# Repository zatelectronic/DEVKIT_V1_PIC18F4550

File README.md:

<div align="center">

# DEVKIT V1 PIC18F4550

**Kit de desenvolvimento profissional para o microcontrolador PIC18F4550 com USB nativo, programação via conector ICSP compatível com programador externo, reguladores 5V e 3,3V, oscilador SMD, botões RESET e BOOT, 2 LEDs de status e exposição completa de todos os ports GPIO**

</div>

---

## 📋 Índice

- [DEVKIT V1 PIC18F4550](#devkit-v1-pic18f4550)
  - [📋 Índice](#-índice)
  - [Visão Geral](#visão-geral)
  - [Renders 3D](#renders-3d)
  - [Arquitetura do Projeto](#arquitetura-do-projeto)
  - [Funcionalidades](#funcionalidades)
  - [Especificações Técnicas](#especificações-técnicas)
  - [Arquitetura de Alimentação](#arquitetura-de-alimentação)
  - [Interface USB Nativa](#interface-usb-nativa)
  - [Conector ICSP — Programação](#conector-icsp--programação)
    - [J5 — ICSP Principal (6 pinos angulado)](#j5--icsp-principal-6-pinos-angulado)
    - [J6 — Conector Auxiliar (3 pinos)](#j6--conector-auxiliar-3-pinos)
  - [Mapa Completo de Conectores e GPIO](#mapa-completo-de-conectores-e-gpio)
    - [J1 — Alimentação Externa (2 pinos)](#j1--alimentação-externa-2-pinos)
    - [J2 — Port RA (5 pinos)](#j2--port-ra-5-pinos)
    - [J3 — Port RC Superior (3 pinos)](#j3--port-rc-superior-3-pinos)
    - [J4 — Port RC Inferior (6 pinos)](#j4--port-rc-inferior-6-pinos)
    - [J7 — Port RE (4 pinos)](#j7--port-re-4-pinos)
    - [J8 — Port RB (4 pinos)](#j8--port-rb-4-pinos)
    - [J9 — Port RD (8 pinos)](#j9--port-rd-8-pinos)
    - [J10 — Alimentações (3 pinos)](#j10--alimentações-3-pinos)
  - [Lista de Materiais](#lista-de-materiais)
    - [Microcontrolador](#microcontrolador)
    - [USB Type-C e Alimentação](#usb-type-c-e-alimentação)
    - [Programador ICSP](#programador-icsp)
    - [Conectores GPIO](#conectores-gpio)
  - [Estrutura do Repositório](#estrutura-do-repositório)
  - [Como Usar](#como-usar)
    - [1. Gravando firmware via ICSP](#1-gravando-firmware-via-icsp)
    - [2. Alimentação](#2-alimentação)
    - [3. Modo Bootloader USB (BOOT)](#3-modo-bootloader-usb-boot)
    - [Exemplo de código — MPLAB XC8](#exemplo-de-código--mplab-xc8)
    - [Ferramentas recomendadas](#ferramentas-recomendadas)
  - [Sobre](#sobre)

---

## Visão Geral

**DEVKIT V1 PIC18F4550** é um kit de desenvolvimento completo para o microcontrolador **PIC18F4550-IPT** (TQFP-44 SMD), projetado pela **ZAT ELECTRONIC** utilizando **KiCad 10** com esquemático hierárquico dividido em quatro sub-folhas: **Microcontrolador**, **USB Type-C**, **Programador ICSP** e **Conexões GPIO**.

O PIC18F4550 é um microcontrolador de 8 bits da família PIC18 com **USB 2.0 Full Speed nativo** (RC4/D− e RC5/D+), memória Flash de 32KB, SRAM de 2KB e EEPROM de 256 bytes. O DEVKIT expõe todos os ports GPIO (RA, RB, RC, RD, RE) em conectores fêmea de 2,54mm, inclui reguladores de tensão **5V** e **3,3V** on-board, oscilador a cristal SMD de **8MHz**, botões **RESET** e **BOOT** tácteis SMD, **2 LEDs SMD** de status e conector **ICSP de 6 pinos** angulado compatível com programador externo.

> 💡 O modelo 3D do programador externo (`Microchip - PICkit3.stp`) está incluído no projeto — as imagens 3D mostram o DEVKIT conectado a um programador externo, evidenciando a integração direta pelo conector ICSP lateral.

---

## Renders 3D

<div align="center">

*Vista superior — PIC18F4550 TQFP-44, USB-C, cristal SMD, botões RESET/BOOT e conectores GPIO*

<br/>

*Vista isométrica — DEVKIT conectado ao programador externo pelo conector ICSP de 6 pinos*

<br/>

*Vista inferior isométrica — exposição completa dos ports RD (8 pinos) e RB (4 pinos) na borda inferior*

<br/>

*Visão completa do ecossistema — DEVKIT + programador externo para gravação de firmware*

</div>

---

## Arquitetura do Projeto

O projeto é organizado em **esquemático hierárquico** com 4 sub-folhas independentes:

```
DEVKIT_V1_PIC18F4550.kicad_sch  (folha raiz)
│
├── MICROCONTROLADOR.kicad_sch
│   ├── PIC18F4550-IPT (TQFP-44)
│   ├── Cristal 8MHz HC-49/SD SMD (KR1)
│   ├── Capacitores de cristal 22pF (C3, C4)
│   ├── Capacitor de desacoplamento USB 470nF (C5)
│   ├── Botão RESET táctil SMD (TACTIL_SWITCH1)
│   ├── Botão BOOT táctil SMD (TACTIL_SWITCH2)
│   ├── LEDs SMD 0805 — L1, L2
│   └── Resistores pull-up/proteção — R5, R6, R7
│
├── TYPE-C_USB.kicad_sch
│   ├── Conector USB-C (USB4105GFA SMD)
│   ├── Regulador 3,3V AMS1117-3.3 (U2 — SOT-223)
│   ├── Diodo Schottky SS1P3L (D1 — DO-220AA)
│   ├── Capacitores eletrolíticos 10µF/16V (C2, C8)
│   ├── Capacitores de desacoplamento 100nF (C1, C6)
│   ├── Resistores CC 5,1KΩ (R3, R4 — para USB-C)
│   ├── Resistores 1KΩ e 0Ω (R1, R2)
│   └── LED SMD (L1 — status alimentação)
│
├── PROGRAMADOR.kicad_sch
│   ├── Conector ICSP 6 pinos angulado (J5)
│   ├── Conector auxiliar de programação (J6)
│   └── Resistores pull-up 10KΩ (R8, R9)
│
└── CONEXÕES.kicad_sch
    ├── J1  — Conector alimentação +5V/GND (2 pinos)
    ├── J2  — Port RA (5 pinos: RA0–RA5)
    ├── J3  — Port RC superior (3 pinos: RC0–RC2)
    ├── J4  — Port RC inferior (6 pinos: RC6, RC7)
    ├── J7  — Port RE (4 pinos: RE0–RE2)
    ├── J8  — Port RB (4 pinos: RB0–RB3)
    ├── J9  — Port RD (8 pinos: RD0–RD7)
    └── J10 — Alimentações (3 pinos: +5V / +3,3V / GND)
```

---

## Funcionalidades

- ✅ **PIC18F4550-IPT** (TQFP-44 SMD) — MCU 8 bits, 32KB Flash, 2KB SRAM, 256B EEPROM
- ✅ **USB 2.0 Full Speed nativo** — RC4/D− e RC5/D+ conectados ao conector USB-C
- ✅ **Conector USB-C** (USB4105GFA SMD) — entrada moderna com resistores CC 5,1KΩ
- ✅ **Regulador 3,3V** (AMS1117-3.3 SOT-223) — saída 3,3V para periféricos de baixa tensão
- ✅ **Alimentação 5V** via USB-C ou conector externo J1
- ✅ **Cristal 8MHz SMD** (HC-49/SD) — oscilador externo de alta estabilidade
- ✅ **Botão RESET** (TACTIL_SWITCH1 — SMD 6×6×6mm) — reset do microcontrolador
- ✅ **Botão BOOT** (TACTIL_SWITCH2 — SMD 6×6×6mm) — entrada em modo bootloader USB
- ✅ **2 LEDs SMD 0805** (L1, L2) — indicadores de status programáveis
- ✅ **Conector ICSP J5** — 6 pinos angulado para programador externo (PGC, PGD, MCLR, VDD, VSS, VPP)
- ✅ **Conector auxiliar J6** — 3 pinos (+5V / PGM / GND) para programação low-voltage
- ✅ **Diodo Schottky SS1P3L** (DO-220AA) — proteção na linha VBUS
- ✅ **Todos os ports GPIO expostos** — RA, RB, RC, RD, RE em conectores fêmea 2,54mm
- ✅ **Capacitores de desacoplamento** distribuídos — C3, C4, C5, C6 (0805 SMD)
- ✅ **Capacitores eletrolíticos** C2, C7, C8 (EIA-3216 SMD) — filtragem de alimentação
- ✅ **4 furos de fixação** — montagem em painéis e caixas
- ✅ **Esquemático hierárquico** em 4 sub-folhas — organização profissional do projeto

---

## Especificações Técnicas

| Parâmetro | Valor |
|-----------|-------|
| **Microcontrolador** | PIC18F4550-IPT |
| **Encapsulamento MCU** | TQFP-44 (10×10mm, passo 0,8mm) |
| **Arquitetura** | 8 bits — PIC18 |
| **Memória Flash** | 32 KB |
| **SRAM** | 2 KB |
| **EEPROM** | 256 bytes |
| **USB** | Full Speed 2.0 nativo (12 Mbps) |
| **Clock** | 8 MHz (cristal externo HC-49/SD SMD) |
| **Tensão de operação** | 2,0V – 5,5V |
| **Tensão da placa** | 5V (USB-C ou J1) |
| **Regulador 3,3V** | AMS1117-3.3 (SOT-223) |
| **Conector USB** | USB-C — USB4105GFA SMD |
| **Conector ICSP** | 6 pinos angulado (PGC/PGD/MCLR/VDD/VSS/VPP) |
| **GPIO exposto** | RA (5), RB (4), RC (7), RD (8), RE (3) = 27 pinos |
| **Botões** | RESET + BOOT (SMD táctil 6×6×6mm) |
| **LEDs** | 2x SMD 0805 |
| **Resistores** | SMD 1206 |
| **Capacitores** | SMD 0805 + EIA-3216 |
| **Ferramenta de Projeto** | KiCad 10 — esquemático hierárquico |
| **Tipo de montagem** | SMD |

---

## Arquitetura de Alimentação

```
USB-C (VBUS 5V)
      │
  [SS1P3L D1]  ← Proteção Schottky
      │
     5V ──────────────────────────────────► J1 (+5V)
      │                                     J10 (+5V)
      │                                     VDD do PIC18F4550
      │
  [AMS1117-3.3 U2]
      │
    3,3V ────────────────────────────────► J10 (+3,3V)
                                           Periféricos 3,3V

Alimentação alternativa:
J1 (+5V / GND) ──► entrada direta de fonte externa 5V
```

---

## Interface USB Nativa

O PIC18F4550 possui **USB 2.0 Full Speed integrado** no próprio chip, sem necessidade de conversor externo:

```
USB-C (USB4105GFA)
    │
    ├── D− (CC1/CC2 com 5,1KΩ) ──► RC4/D− do PIC18F4550
    └── D+ (CC1/CC2 com 5,1KΩ) ──► RC5/D+ do PIC18F4550

R3, R4 (5,1KΩ) — resistores CC para identificação USB-C
C5 (470nF)     — capacitor de desacoplamento USB do PIC
```

> 💡 Para utilizar o USB, o firmware deve implementar a pilha USB do PIC18F4550 via bibliotecas como **Microchip USB Framework** ou **USB CDC** para comunicação serial virtual.

---

## Conector ICSP — Programação

O DEVKIT possui conector **ICSP de 6 pinos angulado (J5)** compatível com programador externo e conectores adicionais:

### J5 — ICSP Principal (6 pinos angulado)

| Pino | Sinal | Descrição |
|------|-------|-----------|
| 1 | PGC | Clock de programação (ICSP Clock) |
| 2 | PGD | Dado de programação (ICSP Data) |
| 3 | VSS | GND |
| 4 | VDD | +5V |
| 5 | VPP | Tensão de programação / MCLR |
| 6 | — | (não conectado) |

### J6 — Conector Auxiliar (3 pinos)

| Pino | Sinal | Descrição |
|------|-------|-----------|
| 1 | +5V | Alimentação |
| 2 | PGM | Low-Voltage Programming |
| 3 | GND | Terra |

> 🔴 Para programar com **programador externo** (ex: PICkit 3/4, ICD): conecte o cabo ICSP no conector J5. O modelo 3D do programador está incluído no projeto para visualização do encaixe.

---

## Mapa Completo de Conectores e GPIO

### J1 — Alimentação Externa (2 pinos)

| Pino | Sinal |
|------|-------|
| 1 | +5V |
| 2 | GND |

### J2 — Port RA (5 pinos)

| Pino | GPIO | Função alternativa |
|------|------|--------------------|
| 1 | RA0 | AN0 / ADC |
| 2 | RA1 | AN1 / ADC |
| 3 | RA2 | AN2 / VREF− |
| 4 | RA3 | AN3 / VREF+ |
| 5 | RA4 | T0CKI / C1OUT |
| 6 | RA5 | AN4 / SS / HLVDIN |

### J3 — Port RC Superior (3 pinos)

| Pino | GPIO | Função alternativa |
|------|------|--------------------|
| 1 | RC0 | T1OSO / T1CKI |
| 2 | RC1 | T1OSI / CCP2 |
| 3 | RC2 | CCP1 |

### J4 — Port RC Inferior (6 pinos)

| Pino | GPIO | Função alternativa |
|------|------|--------------------|
| 1 | RC6 | TX / CK (USART) |
| 2 | RC7 | RX / DT (USART) |

### J7 — Port RE (4 pinos)

| Pino | GPIO | Função alternativa |
|------|------|--------------------|
| 1 | RE0 | AN5 / RD |
| 2 | RE1 | AN6 / WR |
| 3 | RE2 | AN7 / CS |

### J8 — Port RB (4 pinos)

| Pino | GPIO | Função alternativa |
|------|------|--------------------|
| 1 | RB0 | INT0 / FLT0 / AN12 |
| 2 | RB1 | INT1 / AN10 |
| 3 | RB2 | INT2 / AN8 |
| 4 | RB3 | AN9 / CCP2 |

### J9 — Port RD (8 pinos)

| Pino | GPIO | Função alternativa |
|------|------|--------------------|
| 1 | RD0 | PSP0 |
| 2 | RD1 | PSP1 |
| 3 | RD2 | PSP2 |
| 4 | RD3 | PSP3 |
| 5 | RD4 | PSP4 |
| 6 | RD5 | PSP5 |
| 7 | RD6 | PSP6 |
| 8 | RD7 | PSP7 |

### J10 — Alimentações (3 pinos)

| Pino | Sinal |
|------|-------|
| 1 | +5V |
| 2 | +3,3V |
| 3 | GND |

---

## Lista de Materiais

### Microcontrolador

| Ref | Componente | Valor | Encapsulamento |
|-----|-----------|-------|----------------|
| U1 | Microcontrolador | PIC18F4550-IPT | TQFP-44 SMD |
| KR1 | Cristal | 8MHz | HC-49/SD SMD |
| C3, C4 | Capacitor cristal | 22pF | 0805 SMD |
| C5 | Capacitor USB | 470nF / 50V | 0805 SMD |
| TACTIL_SWITCH1 | Botão RESET | 6×6×6mm | SMD táctil |
| TACTIL_SWITCH2 | Botão BOOT | 6×6×6mm | SMD táctil |
| L1, L2 | LED status | SMD 0805 | 0805 SMD |
| R5 | Resistor LED | 1KΩ | 1206 SMD |
| R6 | Resistor pull-up MCLR | 10KΩ | 1206 SMD |
| R7 | Resistor pull-up BOOT | 10KΩ | 1206 SMD |

### USB Type-C e Alimentação

| Ref | Componente | Valor | Encapsulamento |
|-----|-----------|-------|----------------|
| USBC1 | Conector USB-C | USB4105GFA | SMD |
| U2 | Regulador 3,3V | AMS1117-3.3 | SOT-223 SMD |
| D1 | Diodo Schottky | SS1P3L | DO-220AA SMD |
| C1, C6 | Capacitor desacoplamento | 100nF / 50V | 0805 SMD |
| C2, C8 | Capacitor eletrolítico | 10µF / 16V | EIA-3216 SMD |
| C7 | Capacitor eletrolítico | 10µF / 16V | EIA-3216 SMD |
| R1 | Resistor | 0Ω (jumper) | 1206 SMD |
| R2 | Resistor | 1KΩ | 1206 SMD |
| R3, R4 | Resistores CC USB-C | 5,1KΩ | 1206 SMD |

### Programador ICSP

| Ref | Componente | Valor | Encapsulamento |
|-----|-----------|-------|----------------|
| J5 | Conector ICSP | 6 pinos angulado | Header 2,54mm |
| J6 | Conector auxiliar | 3 pinos | Header 2,54mm |
| R8 | Resistor pull-up PGC | 10KΩ | 1206 SMD |
| R9 | Resistor pull-up PGD | 10KΩ | 1206 SMD |

### Conectores GPIO

| Ref | Descrição | Pinos |
|-----|-----------|-------|
| J1 | Alimentação externa | 2 pinos (2,54mm angulado) |
| J2 | Port RA | 5 pinos fêmea 2,54mm |
| J3 | Port RC superior | 3 pinos fêmea 2,54mm |
| J4 | Port RC inferior | 6 pinos fêmea 2,54mm |
| J7 | Port RE | 4 pinos fêmea 2,54mm |
| J8 | Port RB | 4 pinos fêmea 2,54mm |
| J9 | Port RD | 8 pinos fêmea 2,54mm |
| J10 | Alimentações | 3 pinos fêmea 2,54mm |

---

## Estrutura do Repositório

```
DEVKIT_V1_PIC18F4550/
├── DEVKIT_V1_PIC18F4550.kicad_pro    # Arquivo de projeto KiCad
├── DEVKIT_V1_PIC18F4550.kicad_sch    # Esquemático raiz (hierárquico)
├── DEVKIT_V1_PIC18F4550.kicad_pcb    # Layout da PCB (KiCad 10)
├── DEVKIT_V1_PIC18F4550.kicad_prl    # Configurações locais
├── MICROCONTROLADOR.kicad_sch        # Sub-folha: MCU + cristal + botões + LEDs
├── TYPE-C_USB.kicad_sch              # Sub-folha: USB-C + reguladores + proteção
├── PROGRAMADOR.kicad_sch             # Sub-folha: ICSP + conector programador
├── CONEXÕES.kicad_sch                # Sub-folha: todos os conectores GPIO
├── PIC18F4550_DATASHEET.pdf          # Datasheet oficial do PIC18F4550
├── packages3D/                       # Modelos 3D arquivados (STEP / WRL)
│   ├── TQFP-44_10x10mm_P0.8mm.wrl
│   ├── USB4105GFA.STEP
│   ├── SOT-223.wrl
│   ├── Crystal_SMD_HC49-SD.wrl
│   ├── Tactal Switch - SMD 6x6x6.stp
│   ├── LED_0805_2012Metric.wrl
│   ├── D_SMP_DO-220AA.wrl
│   ├── Microchip - PICkit3.stp
│   ├── PinHeader_6X1_right.stp
│   ├── PinHeader_2X1_right.stp
│   └── *-Pin Header - Female - 2.54mm.step
├── fp-info-cache                     # Cache de footprints
├── imagem_1.png                      # Render 3D superior
├── imagem_2.png                      # Render 3D isométrico com programador
├── imagem_3.png                      # Render 3D traseiro
├── imagem_4.png                      # Render 3D completo com programador
└── README.md
```

---

## Como Usar

### 1. Gravando firmware via ICSP

1. Conecte o programador externo ao conector **J5** (6 pinos angulado)
2. Abra o **MPLAB X IDE** e configure o projeto para **PIC18F4550**
3. Selecione o programador (ex: PICkit 3/4) e clique em **Make and Program Device**
4. O LED de status confirmará o sucesso da gravação

### 2. Alimentação

```
Opção A — Via USB-C:
  Conecte cabo USB-C → alimentação automática 5V via VBUS

Opção B — Via conector externo J1:
  Aplique +5V no pino 1 e GND no pino 2 do conector J1
```

### 3. Modo Bootloader USB (BOOT)

```
1. Mantenha o botão BOOT pressionado
2. Pressione e solte o botão RESET
3. Solte o botão BOOT
4. O PIC18F4550 entrará em modo bootloader USB
5. Grave o firmware via software de bootloader (ex: HIDBootloader)
```

### Exemplo de código — MPLAB XC8

```c
#include <xc.h>

// Configurações básicas do PIC18F4550
#pragma config FOSC = HS        // Oscilador externo HS
#pragma config WDT = OFF        // Watchdog desabilitado
#pragma config MCLRE = ON       // MCLR ativo
#pragma config LVP = OFF        // Low-voltage programming off
#pragma config PBADEN = OFF     // PORTB digital

#define _XTAL_FREQ 8000000

void main(void) {
    TRISDbits.TRISD0 = 0;   // RD0 como saída (J9 pino 1)
    TRISDbits.TRISD1 = 0;   // RD1 como saída (J9 pino 2)

    while(1) {
        LATDbits.LATD0 = 1;  // RD0 HIGH
        __delay_ms(500);
        LATDbits.LATD0 = 0;  // RD0 LOW
        __delay_ms(500);
    }
}
```

### Ferramentas recomendadas

| Ferramenta | Finalidade |
|------------|-----------|
| MPLAB X IDE | IDE oficial para desenvolvimento PIC |
| XC8 Compiler | Compilador C para PIC de 8 bits |
| Programador externo | Gravação via ICSP (J5) |
| MPLAB Code Configurator | Geração automática de configuração de periféricos |
| Microchip USB Framework | Implementação da pilha USB do PIC18F4550 |

---

## Sobre

<div align="center">

Projetado por **ZAT ELECTRONIC**

*DEVKIT V1 PIC18F4550 — Made in Brazil 🇧🇷*

</div>

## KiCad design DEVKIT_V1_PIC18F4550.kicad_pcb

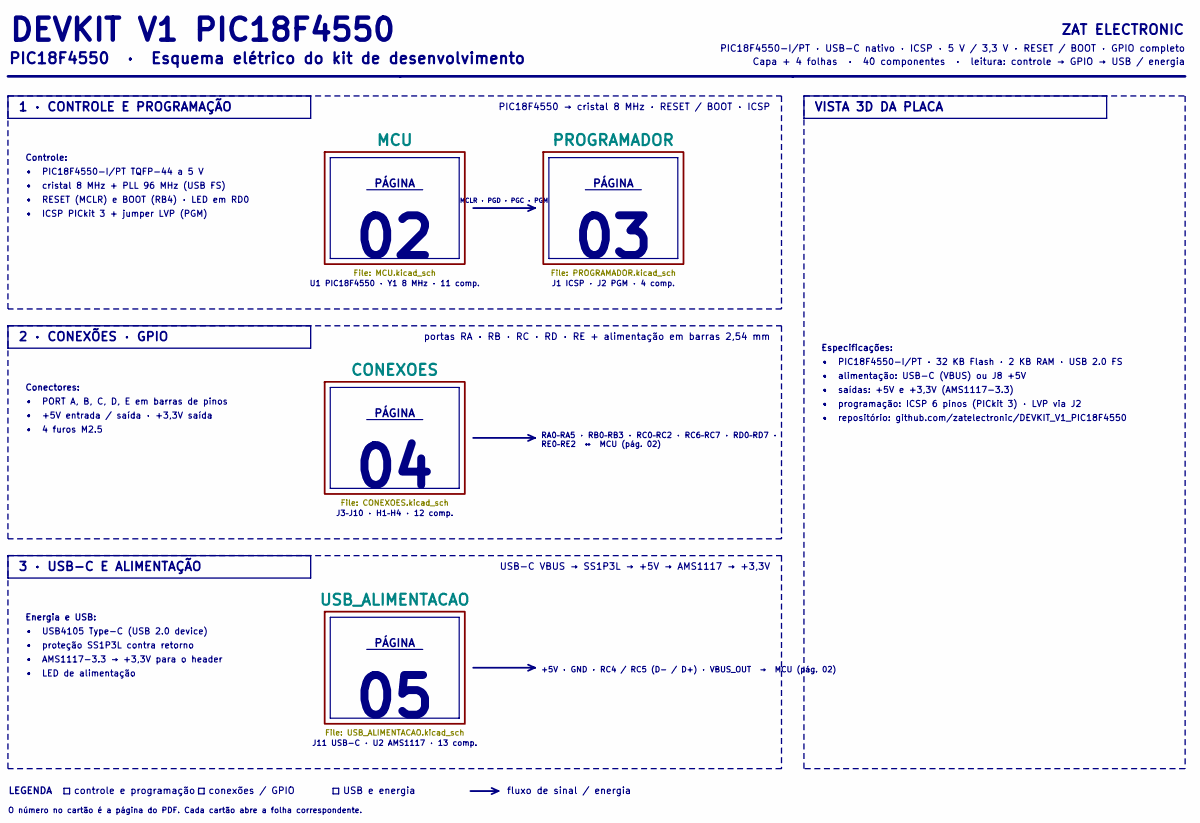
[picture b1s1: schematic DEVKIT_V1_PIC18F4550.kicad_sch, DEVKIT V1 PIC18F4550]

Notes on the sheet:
PÁGINA
• AMS1117-3.3 → +3,3V para o header
• proteção SS1P3L contra retorno
J11 USB-C · U2 AMS1117 · 13 comp.
PIC18F4550 · Esquema elétrico do kit de desenvolvimento
fluxo de sinal / energia
Energia e USB:
2 · CONEXÕES · GPIO
PIC18F4550-I/PT · USB-C nativo · ICSP · 5 V / 3,3 V · RESET / BOOT · GPIO completo
• LED de alimentação
1 · CONTROLE E PROGRAMAÇÃO
Conectores:
U1 PIC18F4550 · Y1 8 MHz · 11 comp.
+5V · GND · RC4 / RC5 (D- / D+) · VBUS_OUT → MCU (pág. 02)
Especificações:
• saídas: +5V e +3,3V (AMS1117-3.3)
• repositório: github.com/zatelectronic/DEVKIT_V1_PIC18F4550
• +5V entrada / saída · +3,3V saída
controle e programação
• PORT A, B, C, D, E em barras de pinos
• RESET (MCLR) e BOOT (RB4) · LED em RD0
MCLR · PGD · PGC · PGM
• PIC18F4550-I/PT TQFP-44 a 5 V
O número no cartão é a página do PDF. Cada cartão abre a folha correspondente.
• USB4105 Type-C (USB 2.0 device)
Capa + 4 folhas · 40 componentes · leitura: controle → GPIO → USB / energia
PIC18F4550 → cristal 8 MHz · RESET / BOOT · ICSP
VISTA 3D DA PLACA
• 4 furos M2.5
USB-C VBUS → SS1P3L → +5V → AMS1117 → +3,3V
J3–J10 · H1–H4 · 12 comp.
J1 ICSP · J2 PGM · 4 comp.
ZAT ELECTRONIC
Controle:
3 · USB-C E ALIMENTAÇÃO
• programação: ICSP 6 pinos (PICkit 3) · LVP via J2
portas RA · RB · RC · RD · RE + alimentação em barras 2,54 mm
RA0–RA5 · RB0–RB3 · RC0–RC2 · RC6–RC7 · RD0–RD7 · RE0–RE2 ↔ MCU (pág. 02)
• PIC18F4550-I/PT · 32 KB Flash · 2 KB RAM · USB 2.0 FS
conexões / GPIO

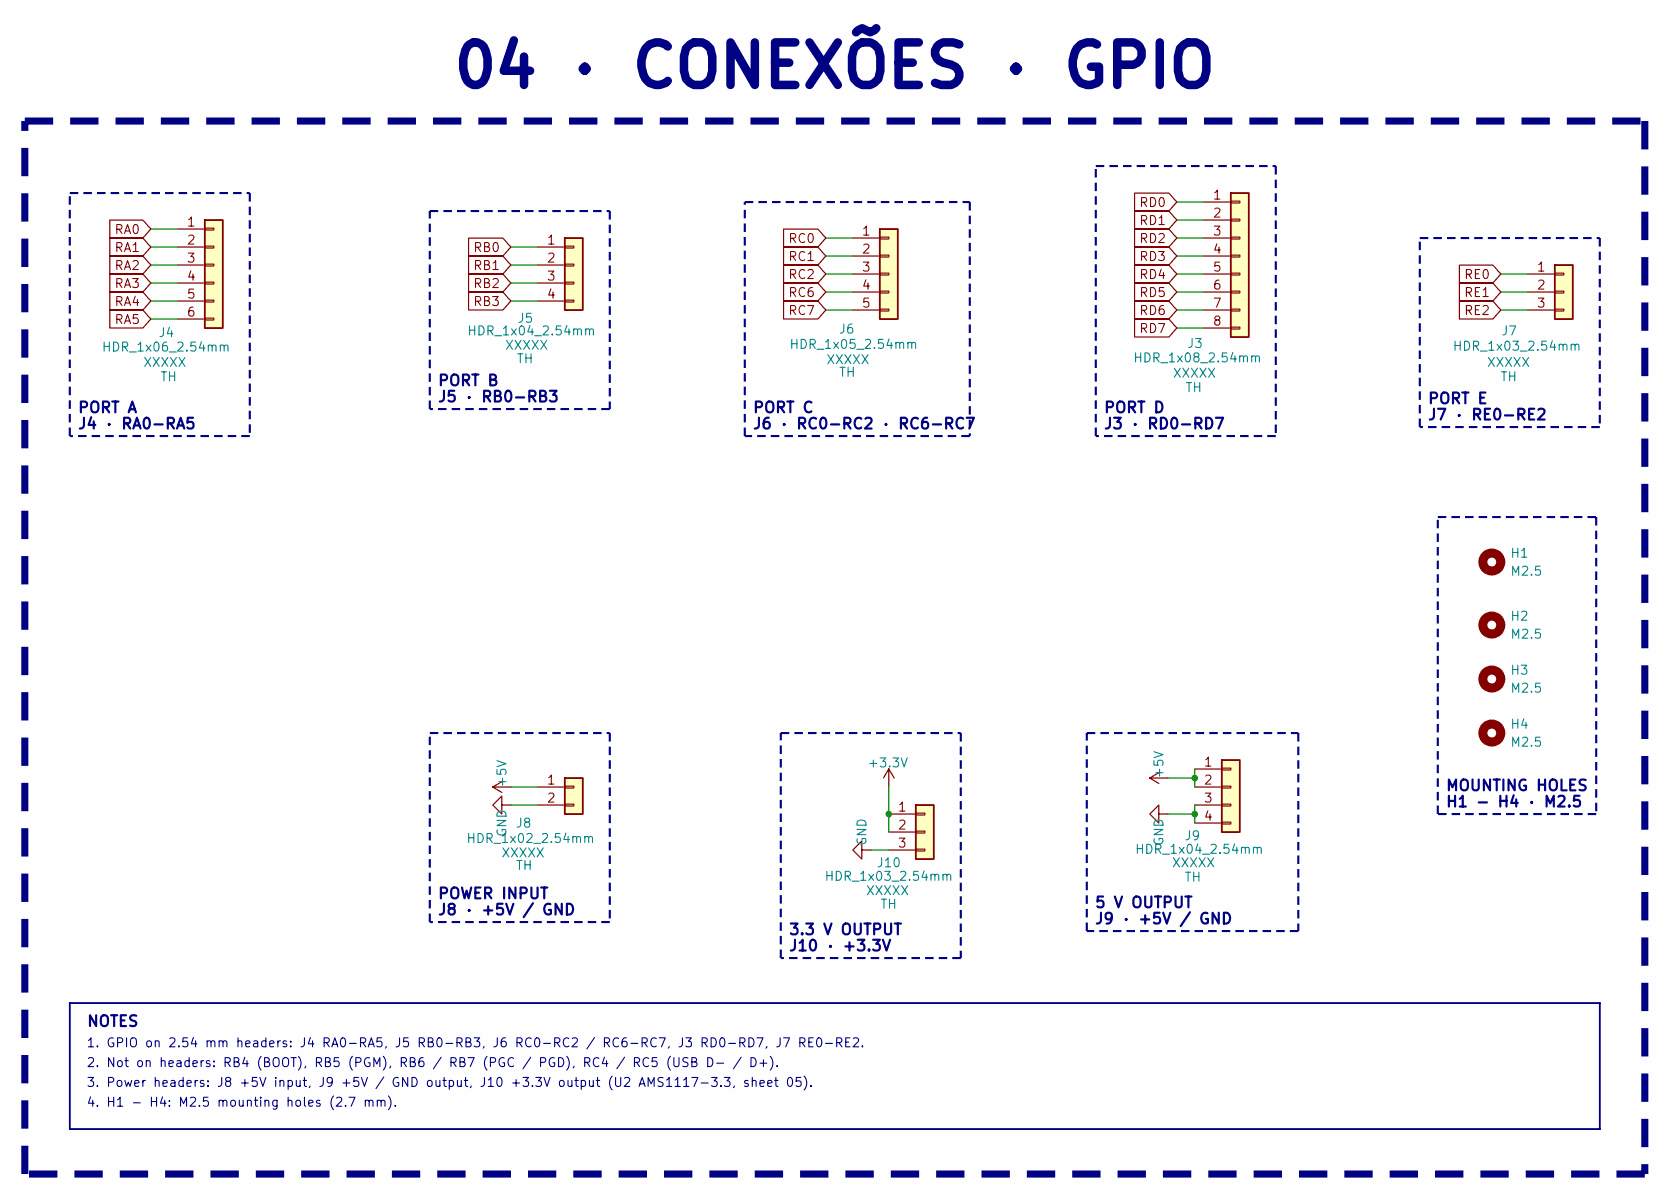
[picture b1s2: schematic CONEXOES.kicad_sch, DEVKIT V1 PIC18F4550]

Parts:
H1, H2, H3, H4: M2.5; MountingHole_2.7mm_M2.5
J3: HDR_1x08_2.54mm; PinHeader_1x08_P2.54mm_Vertical
J4: HDR_1x06_2.54mm; PinHeader_1x06_P2.54mm_Vertical
J5, J9: HDR_1x04_2.54mm; PinHeader_1x04_P2.54mm_Vertical
J6: HDR_1x05_2.54mm; PinHeader_1x05_P2.54mm_Vertical
J7, J10: HDR_1x03_2.54mm; PinHeader_1x03_P2.54mm_Vertical
J8: HDR_1x02_2.54mm; PinHeader_1x02_P2.54mm_Vertical

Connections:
+3.3V: J10.1, J10.2; also elsewhere on the board
+5V: J8.1, J9.1, J9.2; also elsewhere on the board
GND: J8.2, J9.3, J9.4, J10.3; also elsewhere on the board
RA0: J4.1; also elsewhere on the board
RA1: J4.2; also elsewhere on the board
RA2: J4.3; also elsewhere on the board
RA3: J4.4; also elsewhere on the board
RA4: J4.5; also elsewhere on the board
RA5: J4.6; also elsewhere on the board
RB0: J5.1; also elsewhere on the board
RB1: J5.2; also elsewhere on the board
RB2: J5.3; also elsewhere on the board
RB3: J5.4; also elsewhere on the board
RC0: J6.1; also elsewhere on the board
RC1: J6.2; also elsewhere on the board
RC2: J6.3; also elsewhere on the board
RC6: J6.4; also elsewhere on the board
RC7: J6.5; also elsewhere on the board
RD0: J3.1; also elsewhere on the board
RD1: J3.2; also elsewhere on the board
RD2: J3.3; also elsewhere on the board
RD3: J3.4; also elsewhere on the board
RD4: J3.5; also elsewhere on the board
RD5: J3.6; also elsewhere on the board
RD6: J3.7; also elsewhere on the board
RD7: J3.8; also elsewhere on the board
RE0: J7.1; also elsewhere on the board
RE1: J7.2; also elsewhere on the board
RE2: J7.3; also elsewhere on the board

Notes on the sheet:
3. Power headers: J8 +5V input, J9 +5V / GND output, J10 +3.3V output (U2 AMS1117-3.3, sheet 05).
NOTES
PORT A
1. GPIO on 2.54 mm headers: J4 RA0-RA5, J5 RB0-RB3, J6 RC0-RC2 / RC6-RC7, J3 RD0-RD7, J7 RE0-RE2.
H1 - H4 · M2.5
4. H1 - H4: M2.5 mounting holes (2.7 mm).
J7 · RE0-RE2
POWER INPUT
2. Not on headers: RB4 (BOOT), RB5 (PGM), RB6 / RB7 (PGC / PGD), RC4 / RC5 (USB D- / D+).
J3 · RD0-RD7
04 · CONEXÕES · GPIO
J4 · RA0-RA5
MOUNTING HOLES
J8 · +5V / GND
J5 · RB0-RB3
PORT B
PORT D
J10 · +3.3V
PORT C
5 V OUTPUT
3.3 V OUTPUT
PORT E
J6 · RC0-RC2 · RC6-RC7
J9 · +5V / GND

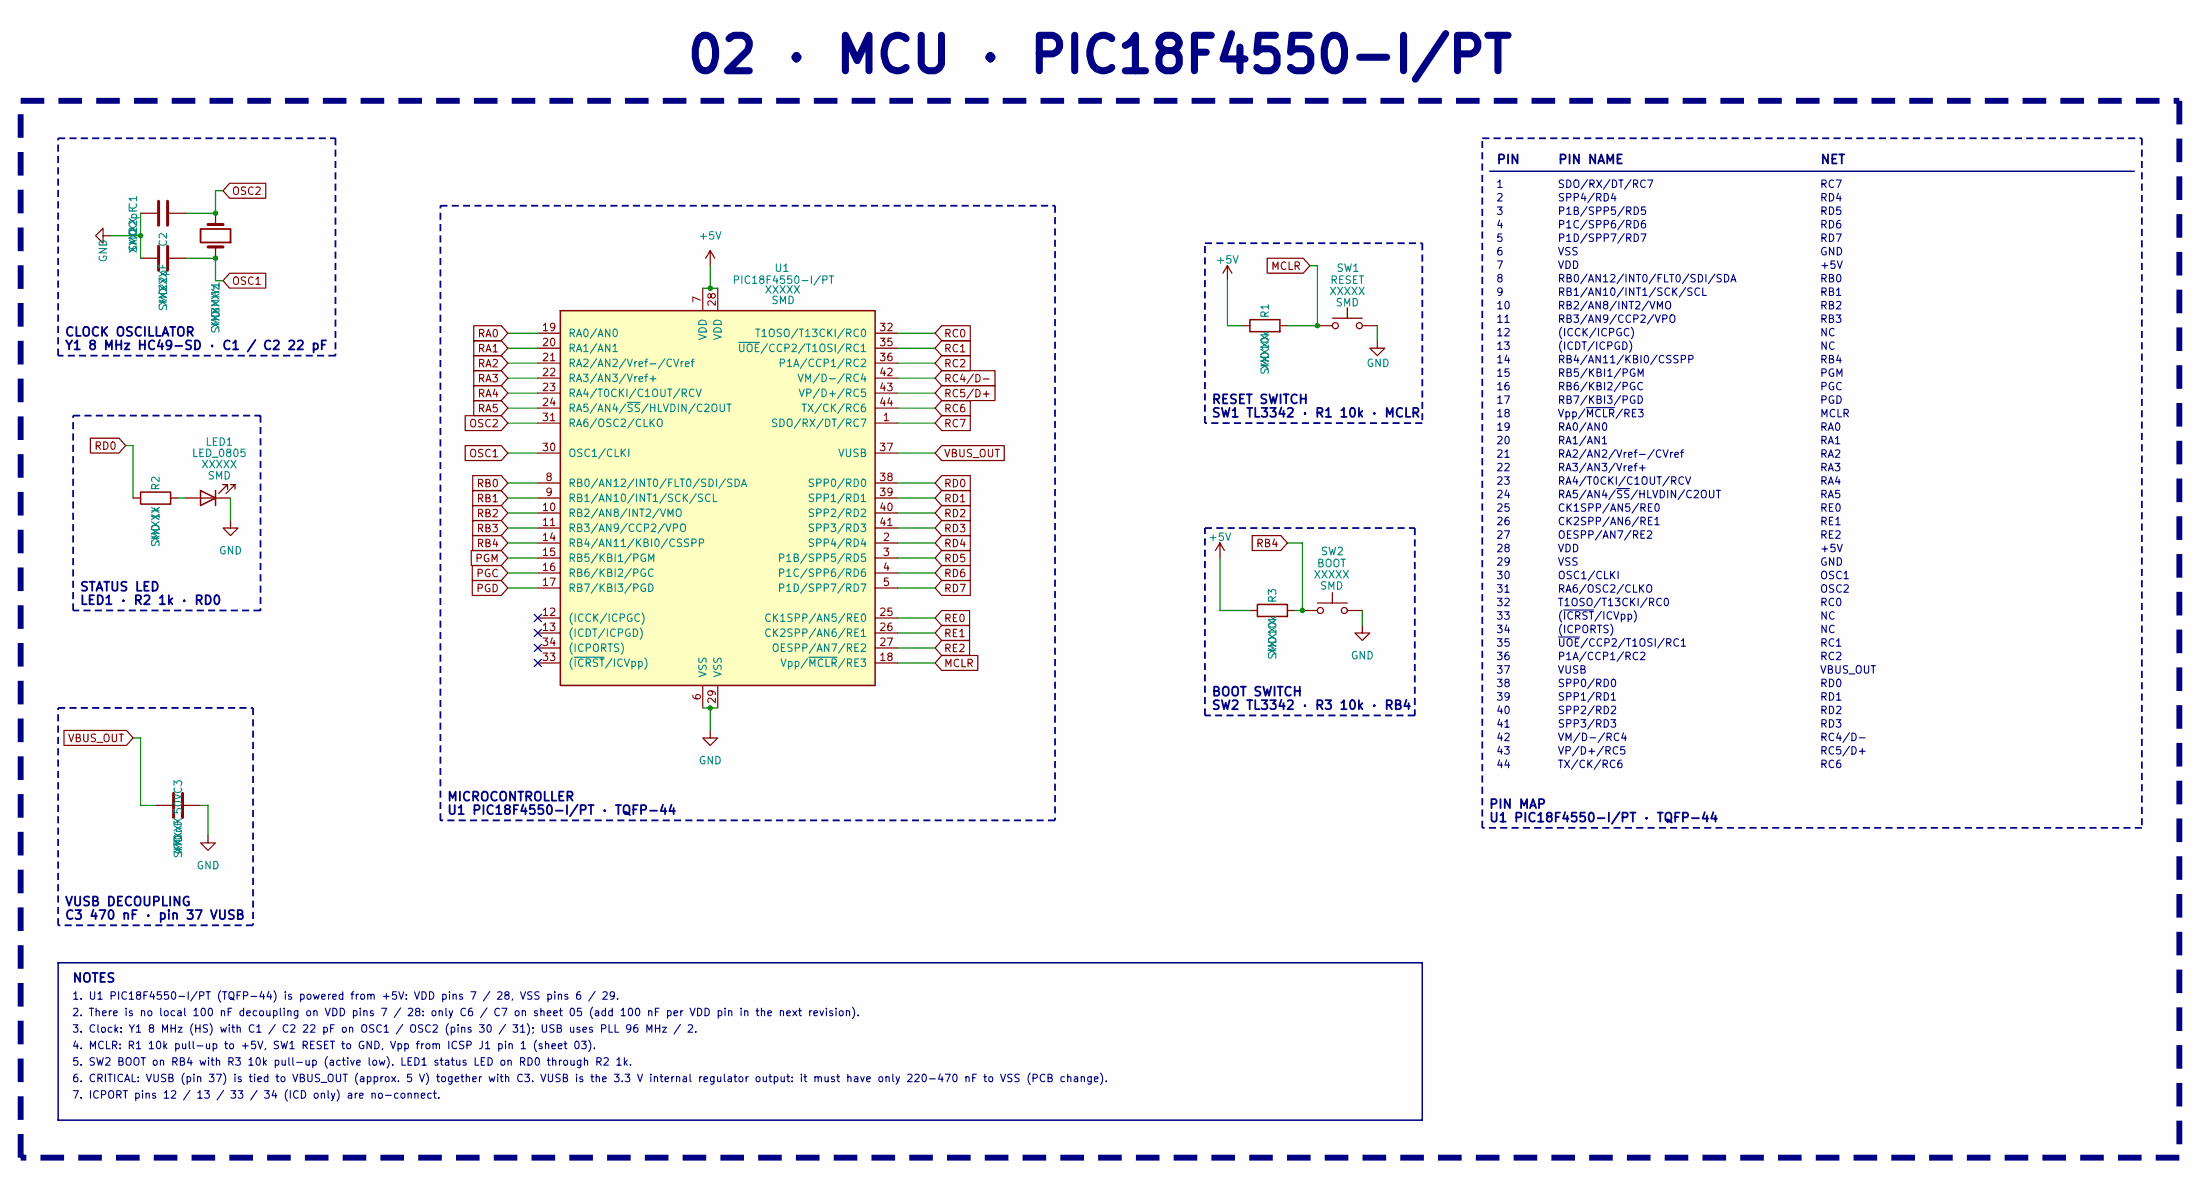
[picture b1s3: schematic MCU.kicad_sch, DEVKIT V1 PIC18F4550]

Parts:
C1, C2: 22pF; C_0805_2012Metric
C3: 470nF 50V; C_0805_2012Metric
LED1: LED_0805; LED_0805_2012Metric
R1, R3: 10k; R_1206_3216Metric
R2: 1k; R_1206_3216Metric
SW1: RESET; SW_SPST_TL3342
SW2: BOOT; SW_SPST_TL3342
U1: PIC18F4550-I/PT; TQFP-44_10x10mm_P0.8mm
Y1: 8MHz; Crystal_SMD_HC49-SD

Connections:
+5V: R1.1, R3.1, U1.7 (VDD), U1.28 (VDD); also elsewhere on the board
GND: C1.2, C2.2, C3.1, LED1.1 (K), SW1.2, SW2.2, U1.6 (VSS), U1.29 (VSS); also elsewhere on the board
MCLR: R1.2, SW1.1, U1.18 (Vpp/~MCLR/RE3); also elsewhere on the board
unnamed: LED1.2 (A), R2.2
OSC1: C2.1, U1.30 (OSC1/CLKI), Y1.1
OSC2: C1.1, U1.31 (RA6/OSC2/CLKO), Y1.2
PGC: U1.16 (RB6/KBI2/PGC); also elsewhere on the board
PGD: U1.17 (RB7/KBI3/PGD); also elsewhere on the board
PGM: U1.15 (RB5/KBI1/PGM); also elsewhere on the board
RA0: U1.19 (RA0/AN0); also elsewhere on the board
RA1: U1.20 (RA1/AN1); also elsewhere on the board
RA2: U1.21 (RA2/AN2/Vref-/CVref); also elsewhere on the board
RA3: U1.22 (RA3/AN3/Vref+); also elsewhere on the board
RA4: U1.23 (RA4/T0CKI/C1OUT/RCV); also elsewhere on the board
RA5: U1.24 (RA5/AN4/~SS/HLVDIN/C2OUT); also elsewhere on the board
RB0: U1.8 (RB0/AN12/INT0/FLT0/SDI/SDA); also elsewhere on the board
RB1: U1.9 (RB1/AN10/INT1/SCK/SCL); also elsewhere on the board
RB2: U1.10 (RB2/AN8/INT2/VMO); also elsewhere on the board
RB3: U1.11 (RB3/AN9/CCP2/VPO); also elsewhere on the board
RB4: R3.2, SW2.1, U1.14 (RB4/AN11/KBI0/CSSPP)
RC0: U1.32 (T1OSO/T13CKI/RC0); also elsewhere on the board
RC1: U1.35 (~UOE/CCP2/T1OSI/RC1); also elsewhere on the board
RC2: U1.36 (P1A/CCP1/RC2); also elsewhere on the board
RC4/D-: U1.42 (VM/D-/RC4); also elsewhere on the board
RC5/D+: U1.43 (VP/D+/RC5); also elsewhere on the board
RC6: U1.44 (TX/CK/RC6); also elsewhere on the board
RC7: U1.1 (SDO/RX/DT/RC7); also elsewhere on the board
RD0: R2.1, U1.38 (SPP0/RD0); also elsewhere on the board
RD1: U1.39 (SPP1/RD1); also elsewhere on the board
RD2: U1.40 (SPP2/RD2); also elsewhere on the board
RD3: U1.41 (SPP3/RD3); also elsewhere on the board
RD4: U1.2 (SPP4/RD4); also elsewhere on the board
RD5: U1.3 (P1B/SPP5/RD5); also elsewhere on the board
RD6: U1.4 (P1C/SPP6/RD6); also elsewhere on the board
RD7: U1.5 (P1D/SPP7/RD7); also elsewhere on the board
RE0: U1.25 (CK1SPP/AN5/RE0); also elsewhere on the board
RE1: U1.26 (CK2SPP/AN6/RE1); also elsewhere on the board
RE2: U1.27 (OESPP/AN7/RE2); also elsewhere on the board
VBUS_OUT: C3.2, U1.37 (VUSB); also elsewhere on the board

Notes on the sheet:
STATUS LED
PIN NAME
4. MCLR: R1 10k pull-up to +5V, SW1 RESET to GND, Vpp from ICSP J1 pin 1 (sheet 03).
VUSB DECOUPLING
RC4/D-
TX/CK/RC6
RA2
RESET SWITCH
1. U1 PIC18F4550-I/PT (TQFP-44) is powered from +5V: VDD pins 7 / 28, VSS pins 6 / 29.
7. ICPORT pins 12 / 13 / 33 / 34 (ICD only) are no-connect.
RE2
RD4
P1A/CCP1/RC2
NET
T1OSO/T13CKI/RC0
GND
RB4/AN11/KBI0/CSSPP
VDD
RC1
RA0
RA1
SDO/RX/DT/RC7
RB2/AN8/INT2/VMO
SPP0/RD0
RC7
~{UOE}/CCP2/T1OSI/RC1
VP/D+/RC5
MCLR
RB1/AN10/INT1/SCK/SCL
RB7/KBI3/PGD
+5V
SW2 TL3342 · R3 10k · RB4
RD2
PIN
VSS
SW1 TL3342 · R1 10k · MCLR
U1 PIC18F4550-I/PT · TQFP-44
5. SW2 BOOT on RB4 with R3 10k pull-up (active low). LED1 status LED on RD0 through R2 1k.
RA4/T0CKI/C1OUT/RCV
(ICPORTS)

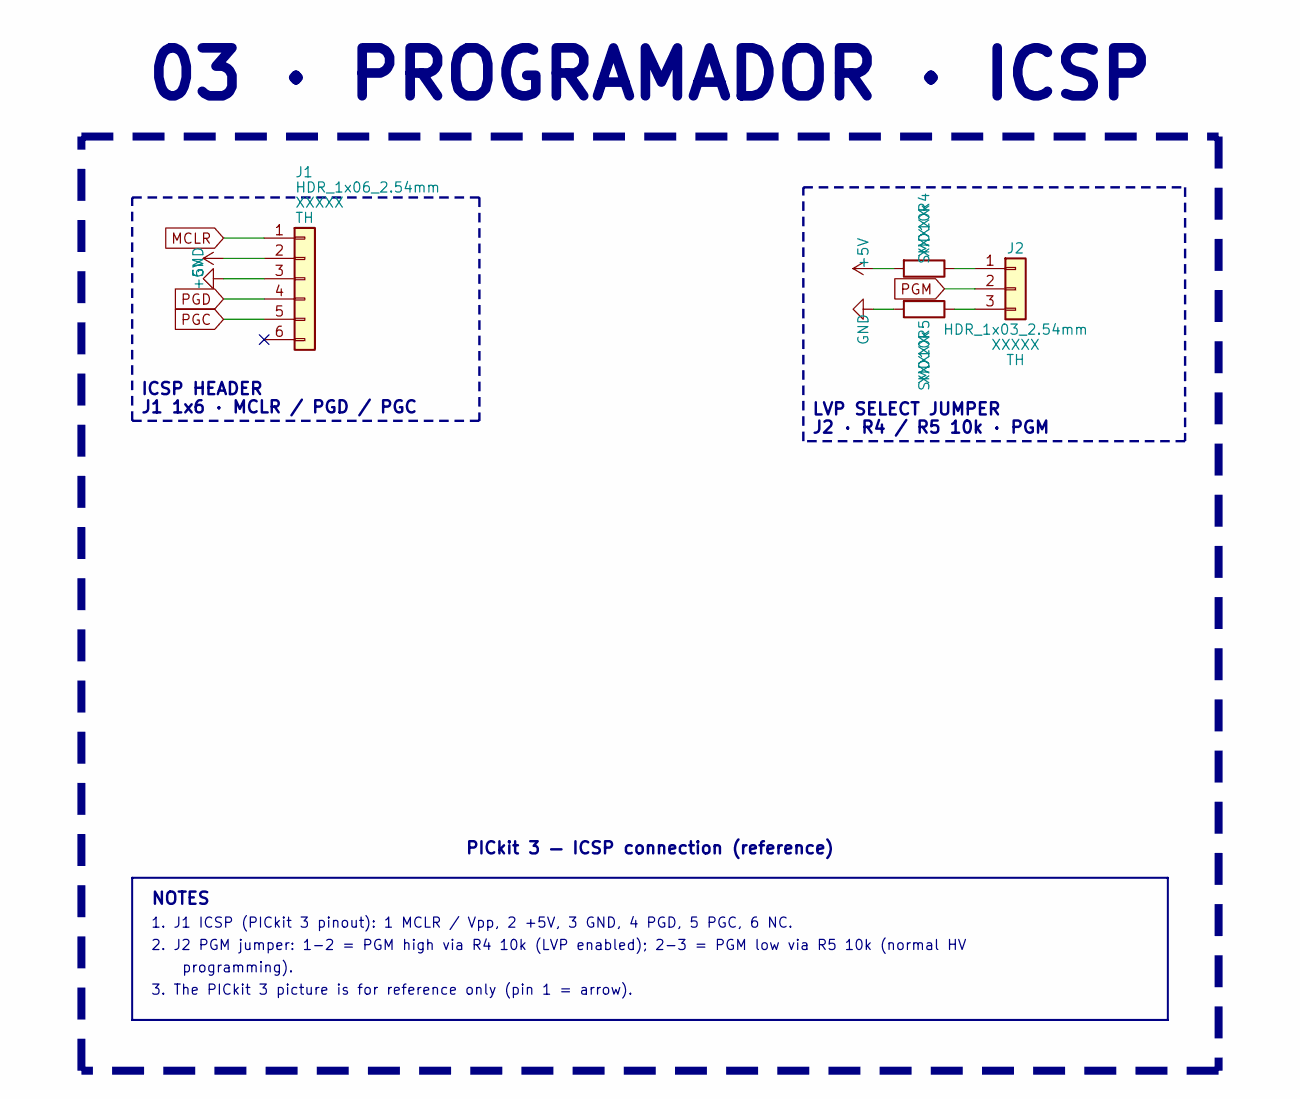
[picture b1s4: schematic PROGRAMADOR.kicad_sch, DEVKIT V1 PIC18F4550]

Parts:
J1: HDR_1x06_2.54mm; PinHeader_1x06_P2.54mm_Vertical
J2: HDR_1x03_2.54mm; PinHeader_1x03_P2.54mm_Vertical
R4, R5: 10k; R_1206_3216Metric

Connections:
+5V: J1.2, R4.2; also elsewhere on the board
GND: J1.3, R5.2; also elsewhere on the board
MCLR: J1.1; also elsewhere on the board
unnamed: J2.1, R4.1
unnamed: J2.3, R5.1
PGC: J1.5; also elsewhere on the board
PGD: J1.4; also elsewhere on the board
PGM: J2.2; also elsewhere on the board

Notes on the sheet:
2. J2 PGM jumper: 1-2 = PGM high via R4 10k (LVP enabled); 2-3 = PGM low via R5 10k (normal HV
NOTES
LVP SELECT JUMPER
J2 · R4 / R5 10k · PGM
ICSP HEADER
PICkit 3 — ICSP connection (reference)
programming).
J1 1x6 · MCLR / PGD / PGC
3. The PICkit 3 picture is for reference only (pin 1 = arrow).
1. J1 ICSP (PICkit 3 pinout): 1 MCLR / Vpp, 2 +5V, 3 GND, 4 PGD, 5 PGC, 6 NC.
03 · PROGRAMADOR · ICSP

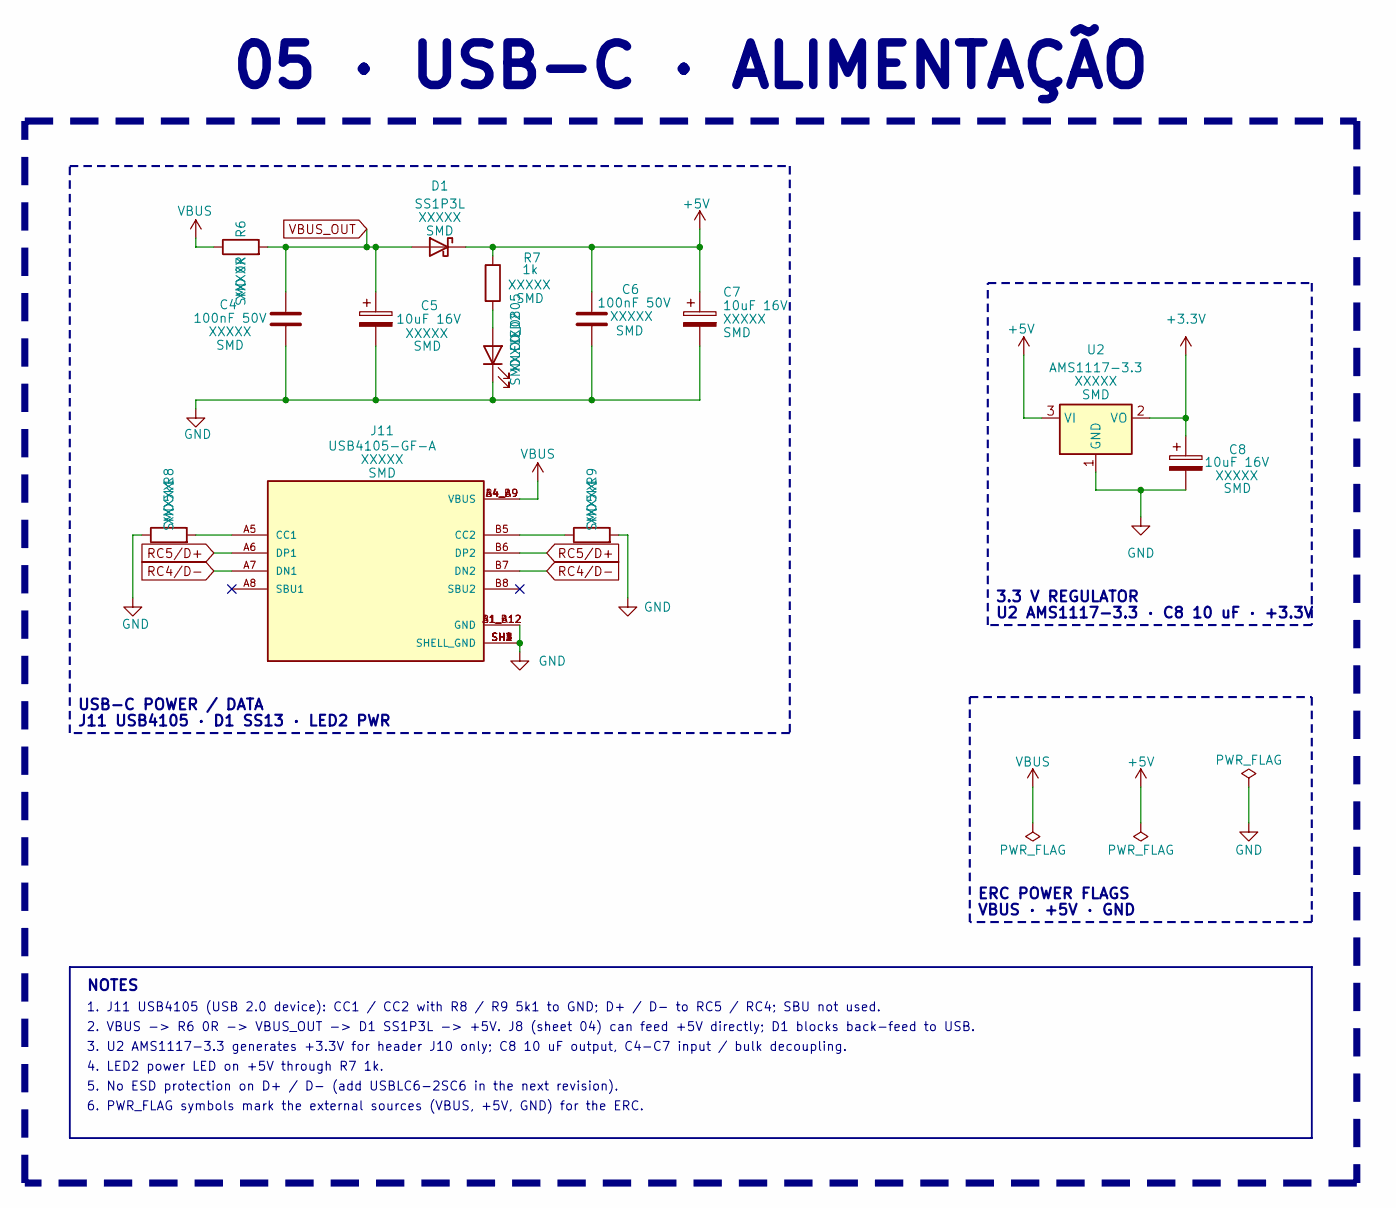
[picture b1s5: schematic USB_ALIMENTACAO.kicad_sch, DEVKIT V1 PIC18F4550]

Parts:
C4, C6: 100nF 50V; C_0805_2012Metric
C5, C7, C8: 10uF 16V; CP_EIA-3216-18_Kemet-A
D1: SS1P3L; D_SMP_DO-220AA
J11: USB4105-GF-A; USB4105GFA
LED2: LED_0805; LED_0805_2012Metric
R6: 0R; R_1206_3216Metric
R7: 1k; R_1206_3216Metric
R8, R9: 5k1; R_1206_3216Metric
U2: AMS1117-3.3; SOT-223-3_TabPin2

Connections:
+3.3V: C8.1, U2.2 (VO); also elsewhere on the board
+5V: C6.1, C7.1, D1.1 (K), R7.1, U2.3 (VI); also elsewhere on the board
GND: C4.2, C5.2, C6.2, C7.2, C8.2, J11.A1_B12 (GND), J11.B1_A12 (GND), J11.SH1 (SHELL_GND), J11.SH2 (SHELL_GND), J11.SH3 (SHELL_GND), J11.SH4 (SHELL_GND), LED2.1 (K), R8.1, R9.2, U2.1 (GND); also elsewhere on the board
unnamed: J11.A5 (CC1), R8.2
unnamed: J11.B5 (CC2), R9.1
unnamed: LED2.2 (A), R7.2
RC4/D-: J11.A7 (DN1), J11.B7 (DN2); also elsewhere on the board
RC5/D+: J11.A6 (DP1), J11.B6 (DP2); also elsewhere on the board
VBUS: J11.A4_B9 (VBUS), J11.B4_A9 (VBUS), R6.1
VBUS_OUT: C4.1, C5.1, D1.2 (A), R6.2; also elsewhere on the board

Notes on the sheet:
3. U2 AMS1117-3.3 generates +3.3V for header J10 only; C8 10 uF output, C4-C7 input / bulk decoupling.
05 · USB-C · ALIMENTAÇÃO
VBUS · +5V · GND
4. LED2 power LED on +5V through R7 1k.
U2 AMS1117-3.3 · C8 10 uF · +3.3V
2. VBUS -> R6 0R -> VBUS_OUT -> D1 SS1P3L -> +5V. J8 (sheet 04) can feed +5V directly; D1 blocks back-feed to USB.
ERC POWER FLAGS
6. PWR_FLAG symbols mark the external sources (VBUS, +5V, GND) for the ERC.
NOTES
USB-C POWER / DATA
3.3 V REGULATOR
5. No ESD protection on D+ / D- (add USBLC6-2SC6 in the next revision).
J11 USB4105 · D1 SS13 · LED2 PWR
1. J11 USB4105 (USB 2.0 device): CC1 / CC2 with R8 / R9 5k1 to GND; D+ / D- to RC5 / RC4; SBU not used.

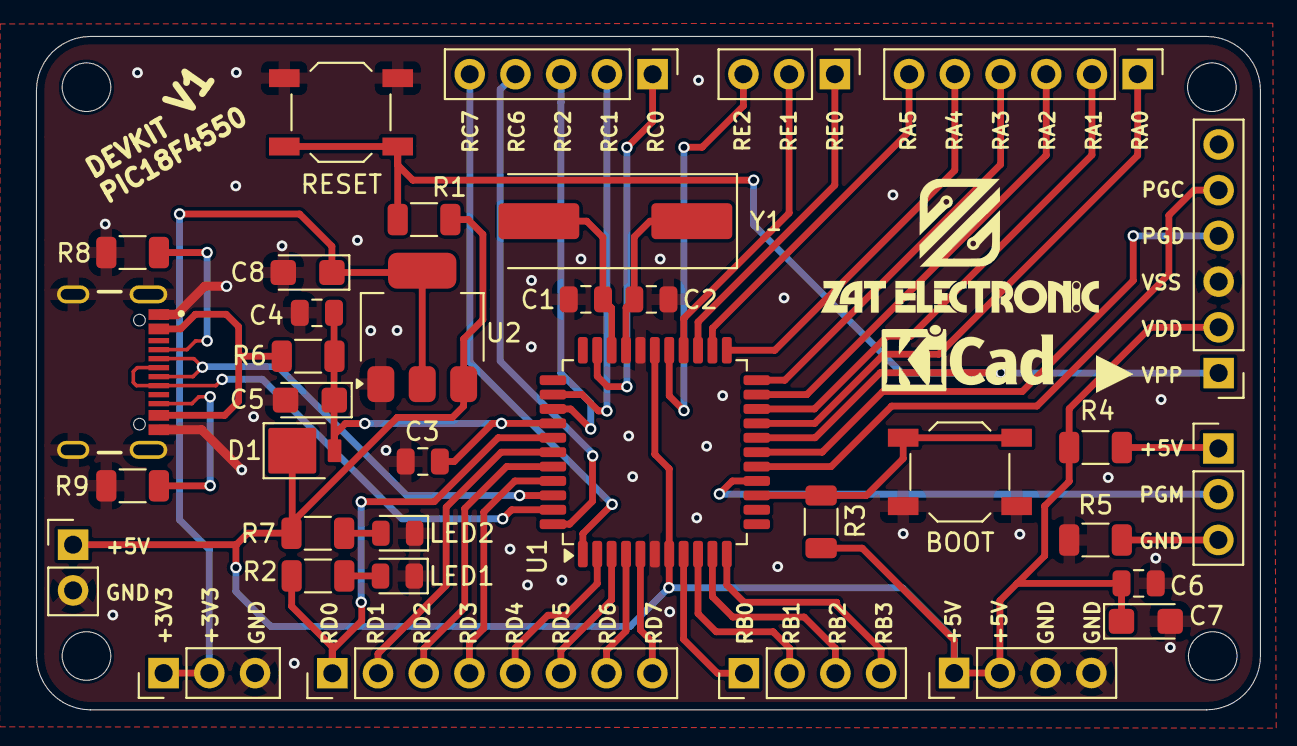
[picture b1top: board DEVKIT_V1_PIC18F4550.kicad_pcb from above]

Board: 2 copper layers, 68.0 x 37.4 mm, 40 parts (0 on the bottom side), 46 nets.

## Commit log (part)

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2026-06-28 commit_3
2026-06-29 COMMIT-4
